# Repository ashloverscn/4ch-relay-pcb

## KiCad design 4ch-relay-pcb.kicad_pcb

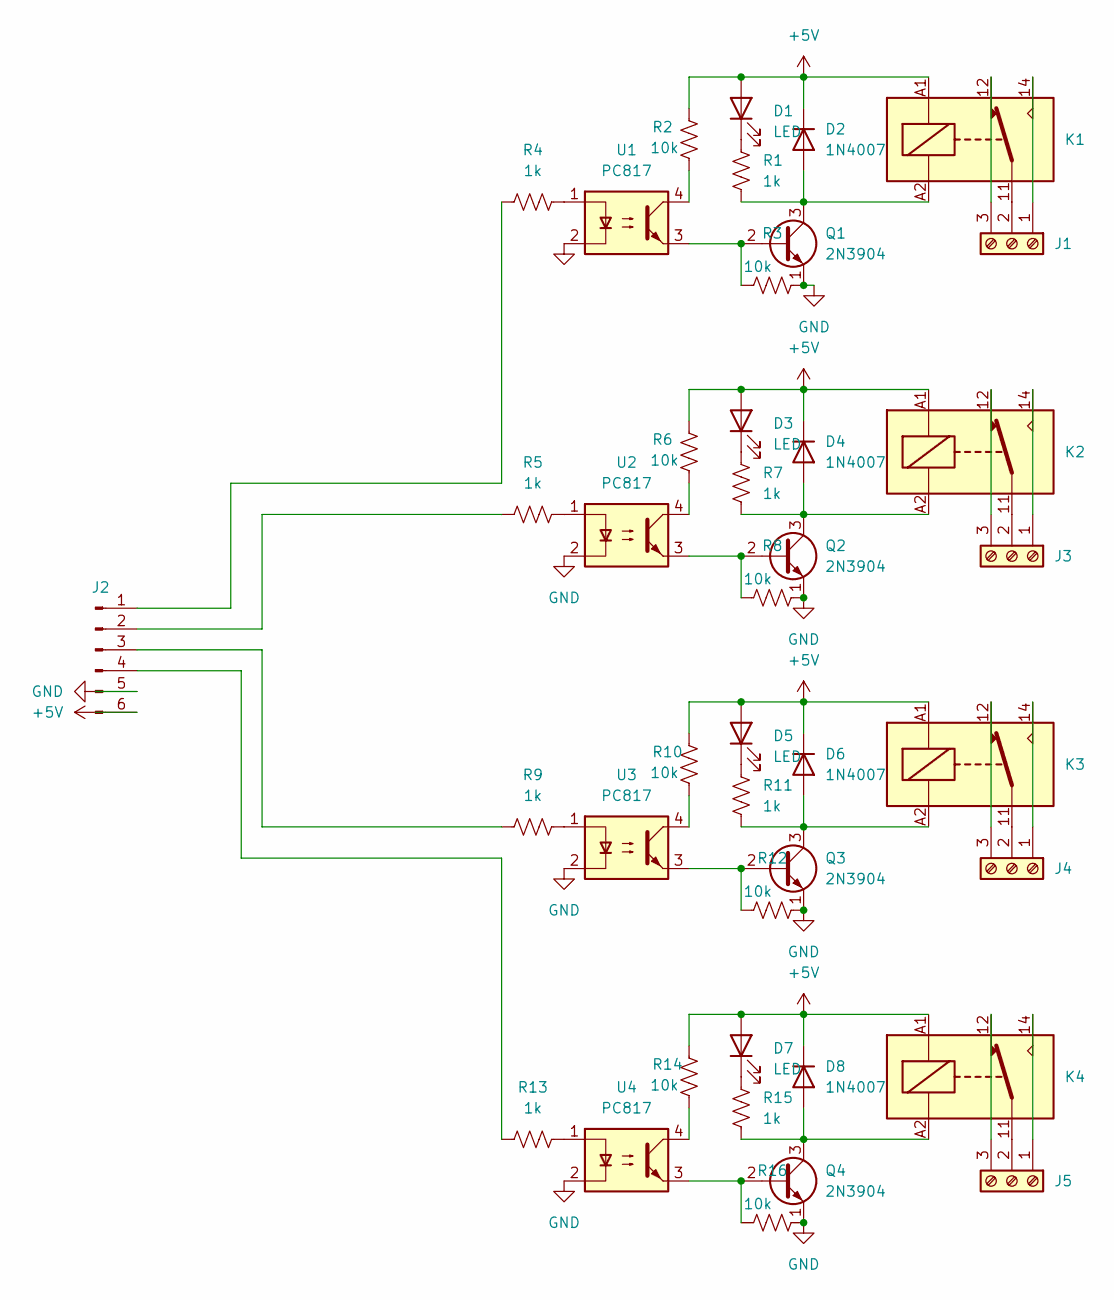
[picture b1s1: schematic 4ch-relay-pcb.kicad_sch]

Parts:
D1, D3, D5, D7: LED; LED_D5.0mm
D2, D4, D6, D8: 1N4007; D_DO-41_SOD81_P10.16mm_Horizontal
J1, J3, J4, J5: Screw_Terminal_01x03; TerminalBlock_Phoenix_MKDS-1,5-3-5.08_1x03_P5.08mm_Horizont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
J2: Conn_01x06_Pin; PinHeader_1x06_P2.54mm_Vertical
K1, K2, K3, K4: Relay_SPDT; Relay_SPDT_Finder_36.11
Q1, Q2, Q3, Q4: 2N3904; TO-92_Inline
R1, R4, R5, R7, R9, R11, R13, R15: 1k; R_Axial_DIN0207_L6.3mm_D2.5mm_P10.16mm_Horizontal
R2, R3, R6, R8, R10, R12, R14, R16: 10k; R_Axial_DIN0207_L6.3mm_D2.5mm_P10.16mm_Horizontal
U1, U2, U3, U4: PC817; DIP-4_W7.62mm

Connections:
+5V: D1.2 (A), D2.1 (K), D3.2 (A), D4.1 (K), D5.2 (A), D6.1 (K), D7.2 (A), D8.1 (K), J2.6, K1.A1, K2.A1, K3.A1, K4.A1, R2.2, R6.2, R10.2, R14.2
GND: J2.5, Q1.1 (E), Q2.1 (E), Q3.1 (E), Q4.1 (E), R3.1, R8.1, R12.1, R16.1, U1.2, U2.2, U3.2, U4.2
unnamed: D1.1 (K), R1.1
unnamed: D2.2 (A), K1.A2, Q1.3 (C), R1.2
unnamed: D3.1 (K), R7.1
unnamed: D4.2 (A), K2.A2, Q2.3 (C), R7.2
unnamed: D5.1 (K), R11.1
unnamed: D6.2 (A), K3.A2, Q3.3 (C), R11.2
unnamed: D7.1 (K), R15.1
unnamed: D8.2 (A), K4.A2, Q4.3 (C), R15.2
unnamed: J1.1, K1.14
unnamed: J1.2, K1.11
unnamed: J1.3, K1.12
unnamed: J2.1, R4.1
unnamed: J2.2, R5.1
unnamed: J2.3, R9.1
unnamed: J2.4, R13.1
unnamed: J3.1, K2.14
unnamed: J3.2, K2.11
unnamed: J3.3, K2.12
unnamed: J4.1, K3.14
unnamed: J4.2, K3.11
unnamed: J4.3, K3.12
unnamed: J5.1, K4.14
unnamed: J5.2, K4.11
unnamed: J5.3, K4.12
unnamed: Q1.2 (B), R3.2, U1.3
unnamed: Q2.2 (B), R8.2, U2.3
unnamed: Q3.2 (B), R12.2, U3.3
unnamed: Q4.2 (B), R16.2, U4.3
unnamed: R2.1, U1.4
unnamed: R4.2, U1.1
unnamed: R5.2, U2.1
unnamed: R6.1, U2.4
unnamed: R9.2, U3.1
unnamed: R10.1, U3.4
unnamed: R13.2, U4.1
unnamed: R14.1, U4.4

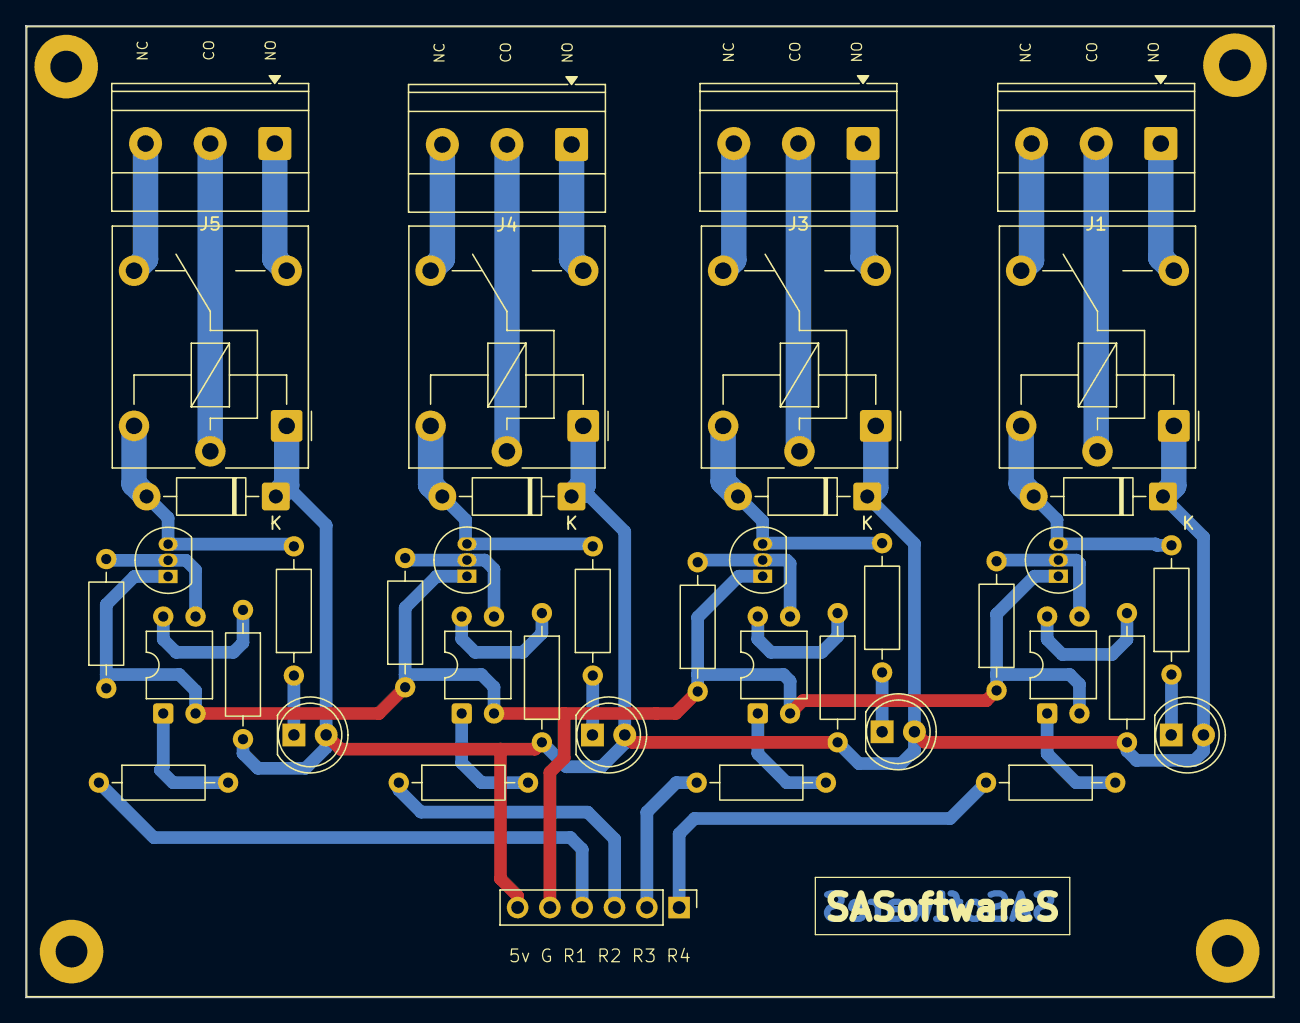
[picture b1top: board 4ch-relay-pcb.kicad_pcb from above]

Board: 2 copper layers, 98.2 x 76.4 mm, 41 parts (0 on the bottom side), 38 nets.
